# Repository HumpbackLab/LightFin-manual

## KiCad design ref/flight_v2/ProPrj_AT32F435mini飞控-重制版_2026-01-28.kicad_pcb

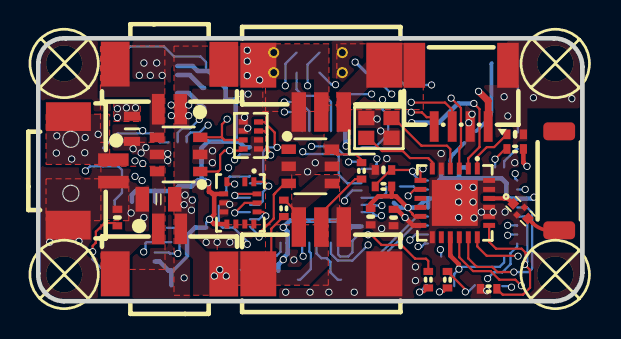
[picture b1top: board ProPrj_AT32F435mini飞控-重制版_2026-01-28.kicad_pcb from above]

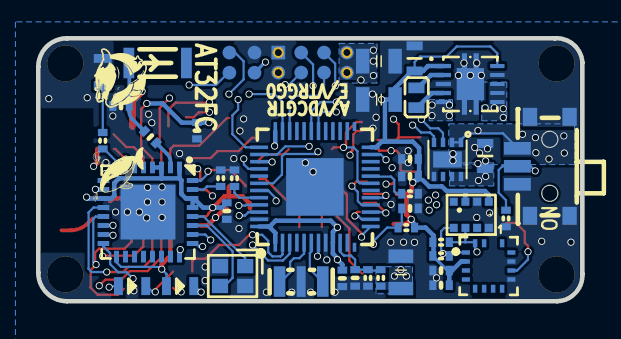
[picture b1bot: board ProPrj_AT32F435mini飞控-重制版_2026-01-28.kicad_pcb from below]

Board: 4 copper layers, 30.2 x 14.6 mm, 82 parts (50 on the bottom side), 64 nets.

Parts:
ANT2: CA-C03
C1, C19, C20: ZC0603
C2, C4, C7, C8, C9, C10, C11, C12, C17, C23, C24, C25, C27, C29, C30: ZC0402
C13, C14, C15, C28: ZC0805
CN1, CN2: CONN-SMD_HC-1.25-3PWT
FL1: FILTER-SMD_4P-L1.0-W0.5-L
L1: ZC0402
L2: IND-SMD_PSTMAA160808-4R7MB
LED1, LED2, LED3: ZLED0603
Q1, Q2: TSOT-23-6_L2.9-W1.6-P0.95-LS2.8-BR
R1, R2, R3, R4, R5, R6, R7, R8, R9, R10, R11, R12, R13, R14, R15, R16, R17: ZR0402
RN1: RES-ARRAY-SMD_0402-8P-L2.0-W1.0-BL
SCREW1, SCREW2, SCREW3, SCREW4: M2螺丝
SW1: SW-SMD_MSK12CO2
TP1, TP3, TP4, TP5, TP6, TP7, TP8, TP9, TP15, TP18: Test-Point-0.5mm
U1: WSON-8_L2.0-W2.0-P0.50-TL-EP
U3: QFN-48_L6.0-W6.0-P0.40-TL-EP3.2
U4: QFN-32_L5.0-W5.0-P0.50-TL-EP3.7
U5: SENSOR-SMD_SPL06-001
U6: QFN-24_L4.0-W4.0-P0.50-BL-EP2.6
U7: LGA-16_L3.0-W3.0-P0.50-BL_SQ
U9: LGA-14L_L3.0-W2.5-P0.50-TL
U10: VSON-10_L3.0-W3.0-P0.50-TL-EP_TPS62410DRCR
U12: CONN-SMD_4P-P1.00_MEGASTAR_ZX-SH1.0-4PWT
U13, U14, U15: CONN-SMD_2P-P1.25_MEGASTAR_ZX-MX1.25-2PWT
U16: OA-C11
X1: OSC-SMD_3P-L3.2-W1.3-P1.2-L
X2, X3: CRYSTAL-SMD_4P-L2.0-W1.6-BL

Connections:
8285_ANT: C2.1, L1.2, U16.1
$1N21: C23.1, U7.10
$1N47: LED1.1, R1.1
$1N48: LED2.1, R3.1
$1N144: R8.2, U3.20
$1N148: R6.1, U4.7
$1N177: C17.2, U6.1
$1N264: R5.2, U4.31
$1N275: LED3.2, R12.2
$1N353: R16.1, SW1.2, U1.3
$1N397: L2.2, U10.2
$1N406: L2.1, U10.4
ADC_VBAT: C4.2, R2.1, R4.2, U3.10
AT32_BOOT: R9.2, U3.44
AT32_NRST: C7.1, R7.1, U3.7
ELRS_LED: R12.1, U4.8
ELRS_RX: TP5.1, U3.40, U4.25
ELRS_TX: TP6.1, U3.39, U4.26
ESP_NRST: C12.1, R10.1, U4.32
GND: C1.1, C4.1, C7.2, C8.1, C9.1, C10.1, C11.1, C12.2, C13.1, C14.1, C15.1, C17.1, C19.1, C20.1, C23.2, C24.1, C25.1, C27.1, C28.1, C29.1, C30.1, CN1.3, CN1.5, CN2.3, FL1.2, FL1.4, L1.1, LED3.1, Q1.2, Q1.5, Q2.2, Q2.5, R4.1, R5.1, R8.1, R9.1, R15.1, R16.2, RN1.3, RN1.4, RN1.7, RN1.8, SCREW1.1, SCREW2.1, SCREW3.1, SCREW4.1, SW1.1, SW1.4, SW1.5, TP1.1, TP9.1, U1.5, U1.9, U3.8, U3.47, U3.49, U4.33, U5.1, U5.7, U6.5, U6.13, U6.20, U6.21, U6.23, U6.24, U6.25, U7.9, U7.11, U9.6, U9.7, U10.3, U10.9, U10.11, U12.2, U12.6, U13.2, U13.3, X1.2, X2.2, X2.4, X3.2, X3.4
GPIO0: TP15.1, U4.15
HEXT_IN: U3.5, X1.3
HEXT_OUT: U3.6, X1.1
IIC2_SCL: R14.1, U3.35, U5.4, U7.1
IIC2_SDA: R13.1, U3.23, U5.3, U7.16
IMU_INT: U3.38, U9.4
LNA: C2.2, U4.2
MOTOR1: Q1.1, RN1.1, U3.42
MOTOR2: Q1.3, RN1.2, U3.43
MOTOR3: Q2.3, RN1.6, U3.13
MOTOR4: Q2.1, RN1.5, U3.19
PWM1: Q1.6, U14.1, U14.4
PWM2: Q1.4, U15.2, U15.3
PWM3: CN1.1, Q2.4, R11.1
PWM4: CN2.1, CN2.4, Q2.6, R17.1, U12.5
RADIO_BUSY: U4.24, U6.7
RADIO_DIO1: U4.16, U6.8
RADIO_MISO: U4.10, U6.16
RADIO_MOSI: U4.12, U6.17
RADIO_NRST: U4.14, U6.3
RADIO_NSS: R15.2, U4.13, U6.19
RADIO_SCK: U4.9, U6.18
RF: FL1.1, U6.22
SPI1_CS: U3.14, U9.12
SPI1_MISO: U3.16, U9.1
SPI1_MOSI: U3.17, U9.14
SPI1_SCK: U3.15, U9.13
SWCLK: TP3.1, U3.37
SWDIO: TP4.1, U3.34
SX1280_RF: ANT2.1, FL1.3
UART1_RX: U3.31, U12.3
UART1_TX: U3.30, U12.4
UART5_RX: TP7.1, U3.45
UART5_TX: TP18.1, U3.46
VBAT: C1.2, C14.2, C15.2, C20.2, C28.2, CN1.2, CN1.4, CN2.2, CN2.5, R2.2, R11.2, R17.2, TP8.1, U1.7, U1.8, U10.5, U10.6, U10.7, U10.8, U12.1, U14.2, U14.3, U15.1, U15.4
VCC: C8.2, C9.2, C10.2, C11.2, C13.2, C19.2, C27.2, C29.2, C30.2, LED1.2, LED2.2, R6.2, R7.2, R10.2, R13.2, R14.2, U3.1, U3.9, U3.24, U3.36, U3.48, U4.1, U4.3, U4.4, U4.11, U4.17, U4.29, U4.30, U5.6, U5.8, U6.11, U6.15, U7.2, U9.5, U9.8, U10.1, U10.10
VDDR: C24.2, C25.2, U6.2, U6.12
VIN: SW1.3, U1.1, U1.2, U1.4, U13.1, U13.4
XTA: U6.4, X3.3
XTAL_IN: U4.28, X2.1
XTAL_OUT: U4.27, X2.3
XTB: U6.6, X3.1
~LED1: R1.2, U3.2
~LED2: R3.2, U3.3

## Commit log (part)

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2026-01-28 更新prompt和完整工程
2026-01-28 完成基本重构
2026-01-28 更新标注
2026-01-29 更新文档和标注
2026-01-29 更新文档
2026-01-30 转为opencode，添加agents.md，更新文档
2026-01-30 增加图片
2026-01-30 更新图片和文档，添加todo待完成
2026-01-30 更新起飞前校准教程
2026-02-01 添加图片和todo
2026-02-01 添加图片、更新文档和todo
2026-02-01 更新文档、完成todo
2026-02-02 添加ci；更新todo版本
2026-02-02 更新ci字体配置
2026-02-02 更新ci和字体
2026-02-02 更新ci release文件名
2026-02-02 修正agents.md
2026-02-02 修正关于串口和LED的描述
2026-02-03 ci增加html输出
2026-02-09 更新产品名称LightFin
2026-02-09 通过压缩图片，优化编译产物体积
2026-02-24 add quick-tutorial.typ.
2026-02-24 update Transmitter binding ways
2026-03-02 fix heading levels
2026-03-02 update action workflow to build all typst sources
2026-04-07 add template to prevent some repeat code.
2026-04-07 remove some unnecessary content in main.
2026-04-07 fix elrs bind description according to quick-tutorial.typ.
2026-04-07 Refine manual connection and firmware update steps
2026-04-07 完善手册编号与更新时间逻辑
2026-04-08 新增英文版主手册及构建流程
2026-05-31 add blackbox guide.
